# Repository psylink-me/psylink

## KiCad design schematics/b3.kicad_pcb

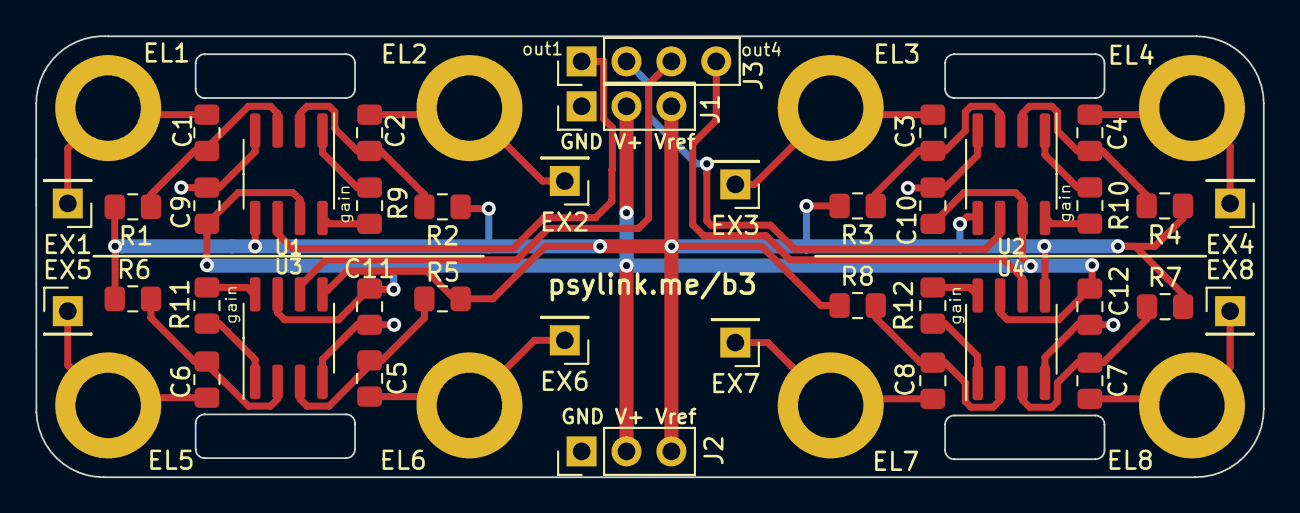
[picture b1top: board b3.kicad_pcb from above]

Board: 2 copper layers, 69.5 x 25.0 mm, 47 parts (0 on the bottom side), 31 nets.

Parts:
C1, C2, C3, C4, C5, C6, C7, C8: 100pF; C_0805_2012Metric_Pad1.15x1.40mm_HandSolder
C9, C10, C11, C12: 100nF; C_0805_2012Metric_Pad1.15x1.40mm_HandSolder
EL1, EL2, EL3, EL4, EL5, EL6, EL7, EL8: Electrode; MountingHole_3.7mm_Pad
EX1, EX2, EX3, EX4, EX5, EX6, EX7, EX8: Conn_01x01; PinHeader_1x01_P2.54mm_Vertical
J1: PowerInput; PinHeader_1x03_P2.54mm_Vertical
J2: PowerPassThru; PinHeader_1x03_P2.54mm_Vertical
J3: OutputPins; PinHeader_1x04_P2.54mm_Vertical
R1, R2, R3, R4, R5, R6, R7, R8: 1M/1%; R_0805_2012Metric_Pad1.15x1.40mm_HandSolder
R9, R10, R11, R12: 1K/1%; R_0805_2012Metric_Pad1.15x1.40mm_HandSolder
U1, U2, U3, U4: INA128; SOIC-8_3.9x4.9mm_P1.27mm

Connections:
/in1: C1.1, EL1.1, EX1.1
/in2: C2.2, EL2.1, EX2.1
/in3: C3.1, EL3.1, EX3.1
/in4: C4.2, EL4.1, EX4.1
/in5: C6.2, EL5.1, EX5.1
/in6: C5.1, EL6.1, EX6.1
/in7: C8.2, EL7.1, EX7.1
/in8: C7.1, EL8.1, EX8.1
/out1: J3.1, U1.6
/out2: J3.2, U2.6
/out3: J3.3, U3.6
/out4: J3.4, U4.6
Earth: C9.2, C10.2, C11.2, C12.2, J1.1, J2.1, U1.4, U2.4, U3.4, U4.4
GNDS: J1.3, J2.3, R1.2, R2.1, R3.2, R4.1, R5.2, R6.1, R7.2, R8.1, U1.5, U2.5, U3.5, U4.5
unnamed: C1.2, R1.1, U1.3
unnamed: C2.1, R2.2, U1.2
unnamed: C3.2, R3.1, U2.3
unnamed: C4.1, R4.2, U2.2
unnamed: C5.2, R5.1, U3.3
unnamed: C6.1, R6.2, U3.2
unnamed: C7.2, R7.1, U4.3
unnamed: C8.1, R8.2, U4.2
unnamed: R9.1, U1.1
unnamed: R9.2, U1.8
unnamed: R10.1, U2.1
unnamed: R10.2, U2.8
unnamed: R11.1, U3.1
unnamed: R11.2, U3.8
unnamed: R12.1, U4.1
unnamed: R12.2, U4.8
VCC: C9.1, C10.1, C11.1, C12.1, J1.2, J2.2, U1.7, U2.7, U3.7, U4.7

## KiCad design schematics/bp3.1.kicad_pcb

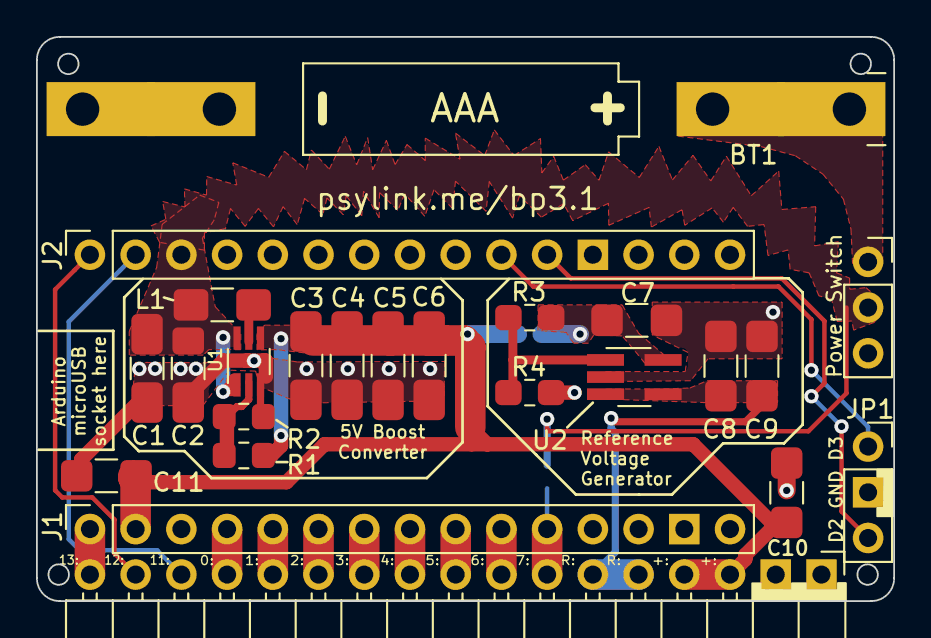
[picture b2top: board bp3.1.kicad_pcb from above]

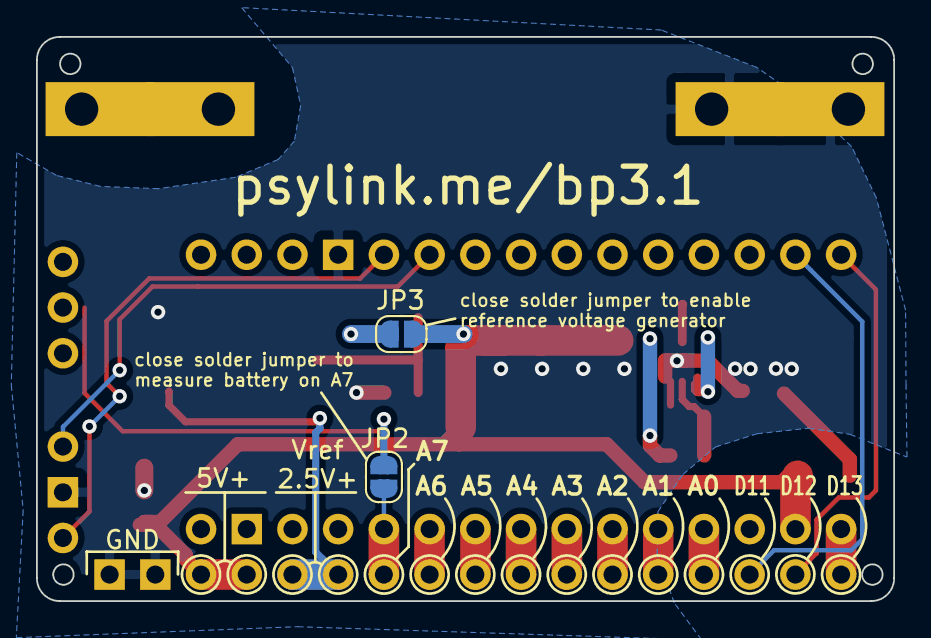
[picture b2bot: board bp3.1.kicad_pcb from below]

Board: 2 copper layers, 47.6 x 31.3 mm, 26 parts (2 on the bottom side), 22 nets.

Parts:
BT1: 1.2V; BatteryHolder_Keystone_82_1xAAA
C1, C2, C3, C4, C5, C6, C7, C8, C9, C10, C11: 100uF; C_1206_3216Metric
J1: Left Pin Strip; PinSocket_1x15_P2.54mm_Vertical
J2: Right Pin Strip; PinSocket_1x15_P2.54mm_Vertical
J3: I/O Pin Strip; PinHeader_1x17_P2.54mm_Horizontal
JP1: Configuration Jumper; PinSocket_1x03_P2.54mm_Vertical
JP2, JP3: Solder Jumper; SolderJumper-2_P1.3mm_Open_RoundedPad1.0x1.5mm
L1: 4.7uH; L_1206_3216Metric_Pad1.42x1.75mm_HandSolder
R1, R3, R4: 1M/1%; R_0805_2012Metric
R2: 110K/1%; R_0805_2012Metric
SW1: Power Switch; PinSocket_1x03_P2.54mm_Vertical
U1: TPS61220DCK; Texas_R-PDSO-G6
U2: LM321; SOT-23-5

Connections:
/A0: J1.4, J3.14
/A1: J1.5, J3.13
/A2: J1.6, J3.12
/A3: J1.7, J3.11
/A4: J1.8, J3.10
/A5: J1.9, J3.9
/A6: J1.10, J3.8
/A7: J1.11, J3.7, JP2.2
/D2: J2.11, JP1.3
/D3: J2.10, JP1.1
/D11: J2.2, J3.15
/D12: J2.1, J3.16
/D13: J1.1, J3.17
/FB: R1.2, R2.1, U1.2
/GND: BT1.2, C1.1, C2.1, C3.2, C4.2, C5.2, C6.2, C7.2, C8.2, C9.2, C10.2, C11.2, J2.12, J3.1, J3.2, JP1.2, R2.2, R4.2, U1.3, U2.2
/L: L1.2, U1.5
/OpAmpV+: C7.1, JP3.2, R3.1, U2.5
/V+: C3.1, C4.1, C5.1, C6.1, C10.1, C11.1, J1.2, J3.3, J3.4, JP3.1, R1.1, U1.4
/Vbat: C1.2, C2.2, J2.3, JP2.1, L1.1, SW1.2, U1.1, U1.6
/Vdiv: R3.2, R4.1, U2.1
/Vref: C8.1, C9.1, J3.5, J3.6, U2.3, U2.4
unnamed: BT1.1, SW1.1
